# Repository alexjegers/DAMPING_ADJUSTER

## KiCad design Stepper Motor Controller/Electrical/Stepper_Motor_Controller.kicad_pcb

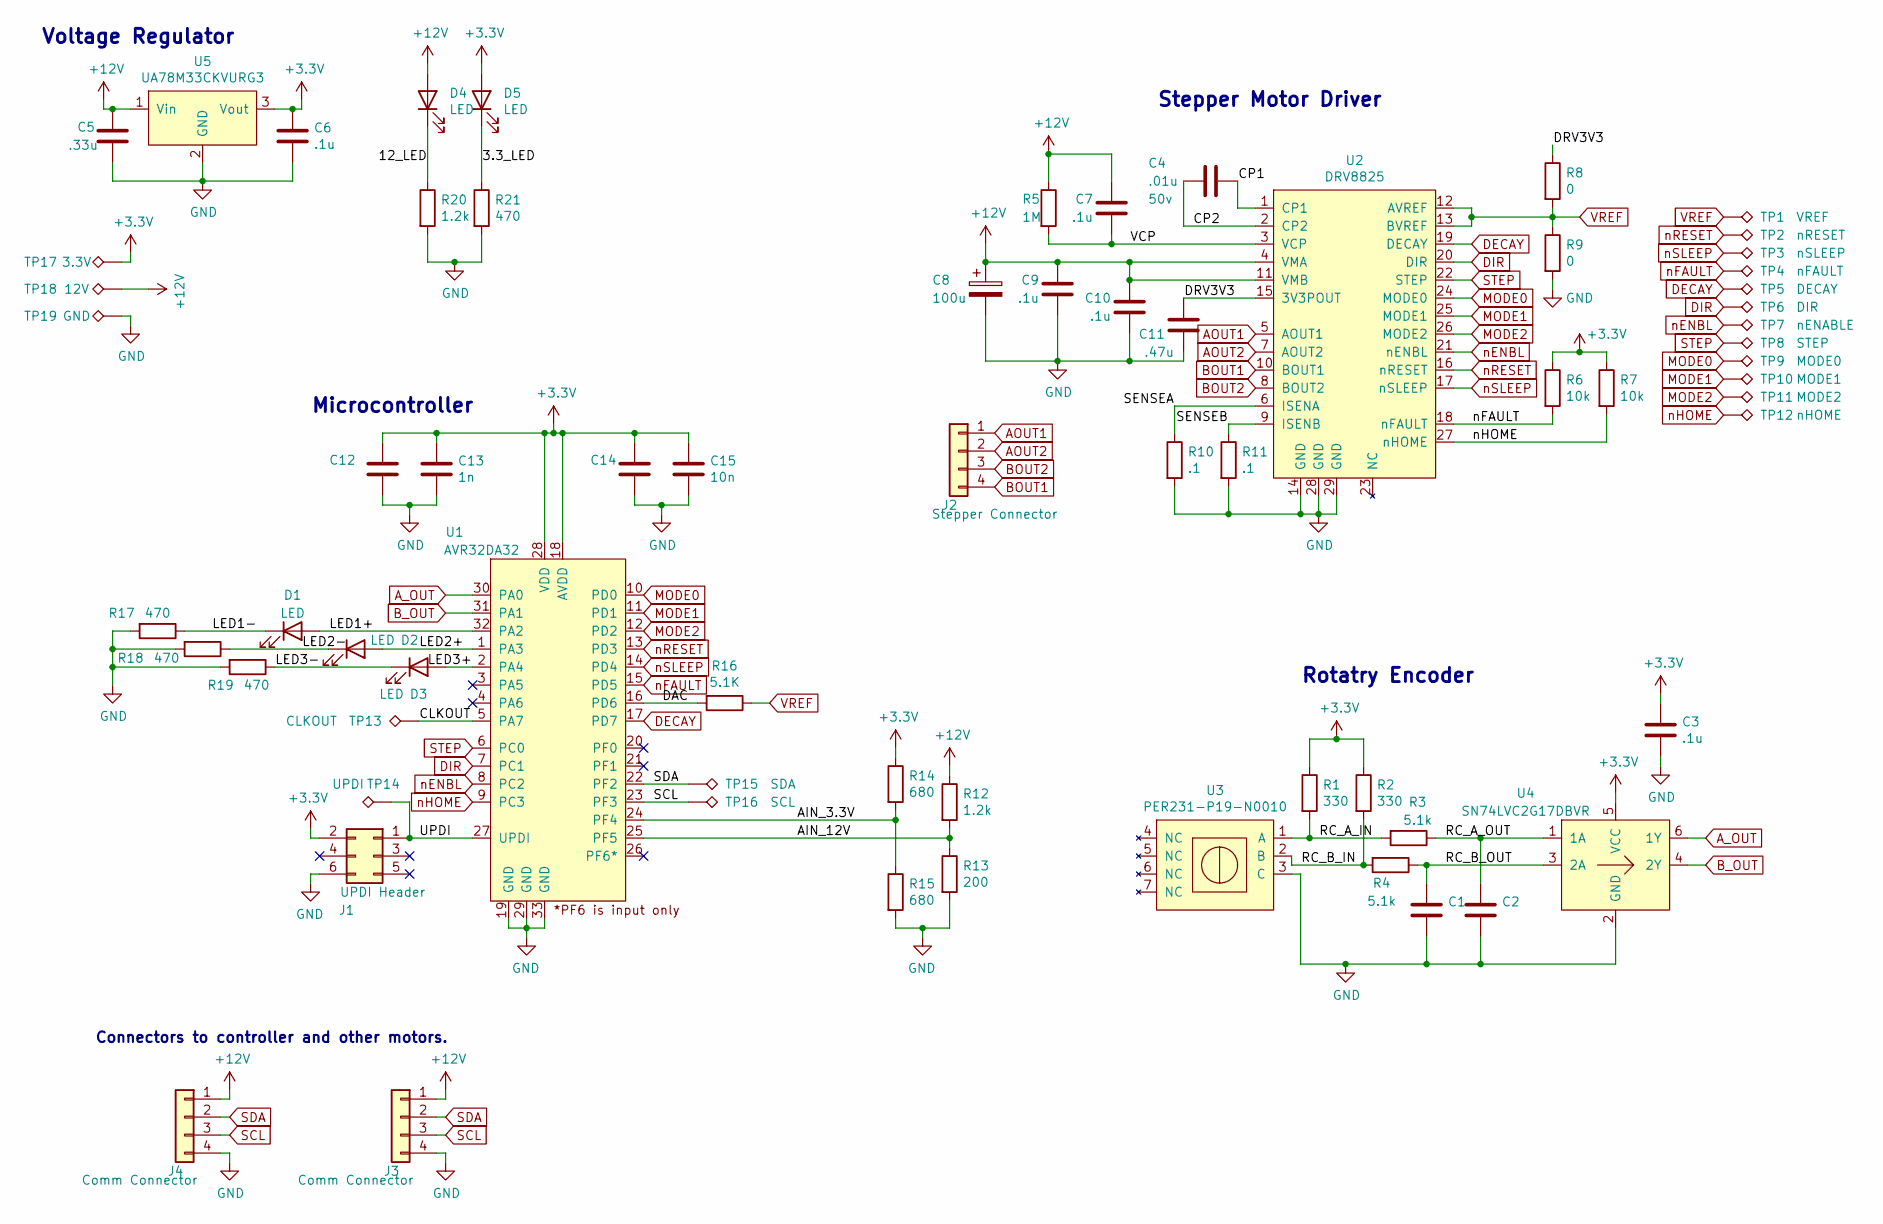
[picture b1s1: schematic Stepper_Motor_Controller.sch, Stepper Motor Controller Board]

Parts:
C1, C2, C12, C14: C_0805_2012Metric
C3, C6, C9, C10: .1u; C_0805_2012Metric
C4: .01u; C_0805_2012Metric; Voltage 50v
C5: .33u; C_0805_2012Metric
C7: .1u; C_0805_2012Metric; Voltage 16v
C8: 100u; CP_Axial_L10.0mm_D6.0mm_P15.00mm_Horizontal; MFG Part # MAL202136101E3
C11: .47u; C_0805_2012Metric; Voltage 6.3V
C13: 1n; C_0805_2012Metric
C15: 10n; C_0805_2012Metric
D1, D2, D3, D4, D5: LED; LED_1206_3216Metric
J1: UPDI Header; PinHeader_2x03_P2.54mm_Vertical
J2: Stepper Connector; 1005-003
J3, J4: Comm Connector; 1005-003
R1, R2: 330; R_0805_2012Metric
R3, R4: 5.1k; R_0805_2012Metric
R5: 1M; R_0805_2012Metric
R6, R7: 10k; R_0805_2012Metric
R8, R9: 0; R_0805_2012Metric
R10, R11: .1; R_1206_3216Metric; MFG Part # KDV12DR100ET
R12, R20: 1.2k; R_0805_2012Metric
R13: 200; R_0805_2012Metric
R14, R15: 680; R_0805_2012Metric
R16: 5.1K; R_0805_2012Metric
R17, R18, R19, R21: 470; R_0805_2012Metric
TP1: VREF; TestPoint_Pad_1.5x1.5mm
TP2: nRESET; TestPoint_Pad_1.5x1.5mm
TP3: nSLEEP; TestPoint_Pad_1.5x1.5mm
TP4: nFAULT; TestPoint_Pad_1.5x1.5mm
TP5: DECAY; TestPoint_Pad_1.5x1.5mm
TP6: DIR; TestPoint_Pad_1.5x1.5mm
TP7: nENABLE; TestPoint_Pad_1.5x1.5mm
TP8: STEP; TestPoint_Pad_1.5x1.5mm
TP9: MODE0; TestPoint_Pad_1.5x1.5mm
TP10: MODE1; TestPoint_Pad_1.5x1.5mm
TP11: MODE2; TestPoint_Pad_1.5x1.5mm
TP12: nHOME; TestPoint_Pad_1.5x1.5mm
TP13: CLKOUT; TestPoint_Pad_1.5x1.5mm
TP14: UPDI; TestPoint_Pad_1.5x1.5mm
TP15: SDA; TestPoint_Pad_1.5x1.5mm
TP16: SCL; TestPoint_Pad_1.5x1.5mm
TP17: 3.3V; TestPoint_Pad_1.5x1.5mm
TP18: 12V; TestPoint_Pad_1.5x1.5mm
TP19: GND; TestPoint_Pad_1.5x1.5mm
U1: AVR32DA32; QFN-32-1EP_5x5mm_P0.5mm_EP3.1x3.1mm
U2: DRV8825; HTSSOP-28-1EP_4.4x9.7mm_P0.65mm_EP2.85x5.4mm_ThermalVias
U3: PER231-P19-N0010
U4: SN74LVC2G17DBVR; SOT-23-6_Handsoldering
U5: UA78M33CKVURG3; TO-252-2

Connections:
+3V3: C3.1, C6.1, C12.1, C13.1, C14.1, C15.1, D5.2 (A), J1.2, R1.1, R2.1, R6.1, R7.1, R14.1, TP17.1, U1.18 (AVDD), U1.28 (VDD), U4.5 (VCC), U5.3 (Vout)
+12V: C5.1, C7.2, C8.1, C9.2, C10.2, D4.2 (A), J3.1, J4.1, R5.1, R12.1, TP18.1, U2.4 (VMA), U2.11 (VMB), U5.1 (Vin)
/3.3_LED: D5.1 (K), R21.1
/12_LED: D4.1 (K), R20.1
/AIN_3.3V: R14.2, R15.1, U1.24 (PF4)
/AIN_12V: R12.2, R13.1, U1.25 (PF5)
/CLKOUT: TP13.1, U1.5 (PA7)
/CP1: C4.2, U2.1 (CP1)
/CP2: C4.1, U2.2 (CP2)
/DAC: R16.2, U1.16 (PD6)
/DRV3V3: C11.2, R8.1, U2.15 (3V3POUT)
/LED1+: D1.2 (A), U1.32 (PA2)
/LED1-: D1.1 (K), R17.1
/LED2+: D2.2 (A), U1.1 (PA3)
/LED2-: D2.1 (K), R18.1
/LED3+: D3.2 (A), U1.2 (PA4)
/LED3-: D3.1 (K), R19.1
/RC_A_IN: R1.2, R3.2, U3.1 (A)
/RC_A_OUT: C2.1, R3.1, U4.1 (1A)
/RC_B_IN: R2.2, R4.2, U3.2 (B)
/RC_B_OUT: C1.1, R4.1, U4.3 (2A)
/SENSEA: R10.1, U2.6 (ISENA)
/SENSEB: R11.1, U2.9 (ISENB)
/UPDI: J1.1, TP14.1, U1.27 (UPDI)
/VCP: C7.1, R5.2, U2.3 (VCP)
AOUT1: J2.1, U2.5 (AOUT1)
AOUT2: J2.2, U2.7 (AOUT2)
A_OUT: U1.30 (PA0), U4.6 (1Y)
BOUT1: J2.4, U2.10 (BOUT1)
BOUT2: J2.3, U2.8 (BOUT2)
B_OUT: U1.31 (PA1), U4.4 (2Y)
DECAY: TP5.1, U1.17 (PD7), U2.19 (DECAY)
DIR: TP6.1, U1.7 (PC1), U2.20 (DIR)
GND: C1.2, C2.2, C3.2, C5.2, C6.2, C8.2, C9.1, C10.1, C11.1, C12.2, C13.2, C14.2, C15.2, J1.6, J3.4, J4.4, R9.2, R10.2, R11.2, R13.2, R15.2, R17.2, R18.2, R19.2, R20.2, R21.2, TP19.1, U1.19 (GND), U1.29 (GND), U1.33 (GND), U2.14 (GND), U2.28 (GND), U2.29 (GND), U3.3 (C), U4.2 (GND), U5.2 (GND)
MODE0: TP9.1, U1.10 (PD0), U2.24 (MODE0)
MODE1: TP10.1, U1.11 (PD1), U2.25 (MODE1)
MODE2: TP11.1, U1.12 (PD2), U2.26 (MODE2)
SCL: J3.3, J4.3, TP16.1, U1.23 (PF3)
SDA: J3.2, J4.2, TP15.1, U1.22 (PF2)
STEP: TP8.1, U1.6 (PC0), U2.22 (STEP)
VREF: R8.2, R9.1, R16.1, TP1.1, U2.12 (AVREF), U2.13 (BVREF)
nENBL: TP7.1, U1.8 (PC2), U2.21 (nENBL)
nFAULT: R6.2, TP4.1, U1.15 (PD5), U2.18 (nFAULT)
nHOME: R7.2, TP12.1, U1.9 (PC3), U2.27 (nHOME)
nRESET: TP2.1, U1.13 (PD3), U2.16 (nRESET)
nSLEEP: TP3.1, U1.14 (PD4), U2.17 (nSLEEP)

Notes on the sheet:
Connectors to controller and other motors.
Microcontroller
Voltage Regulator
Stepper Motor Driver
Rotatry Encoder

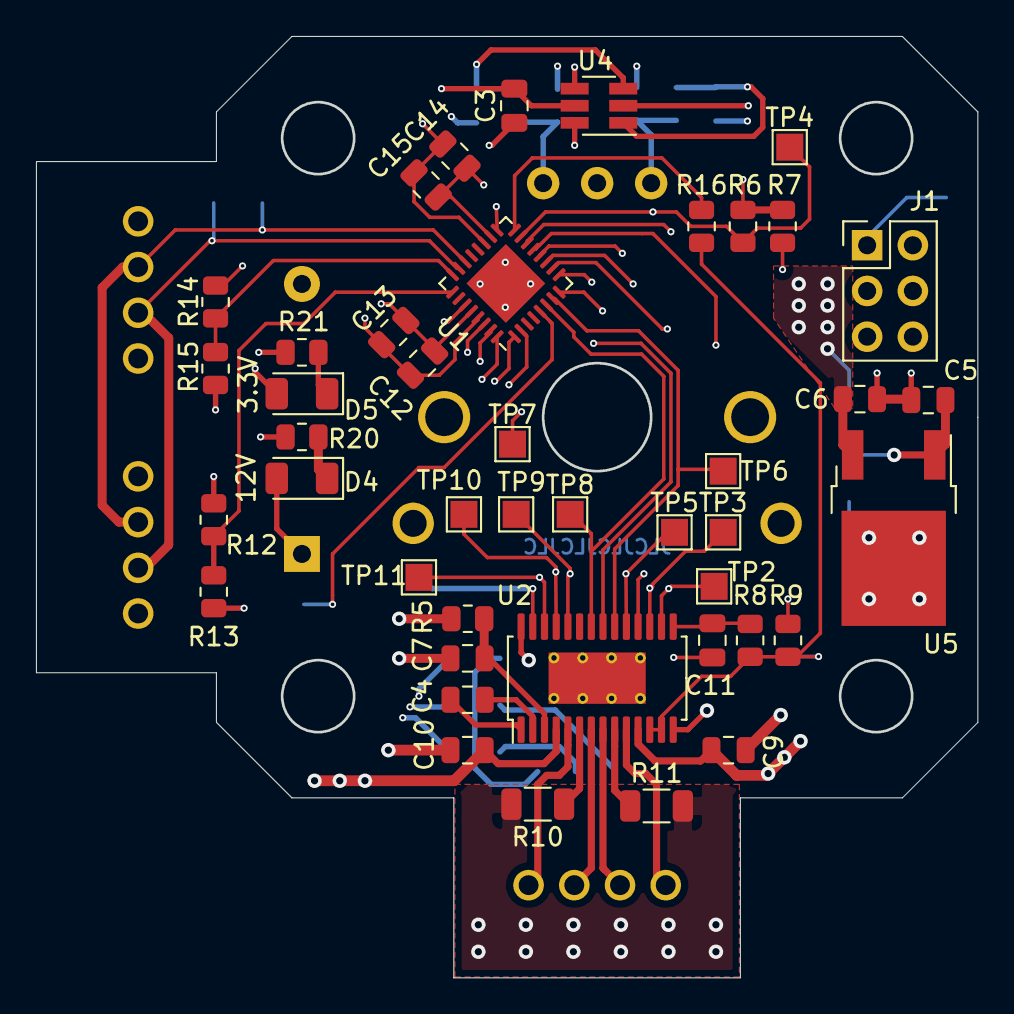
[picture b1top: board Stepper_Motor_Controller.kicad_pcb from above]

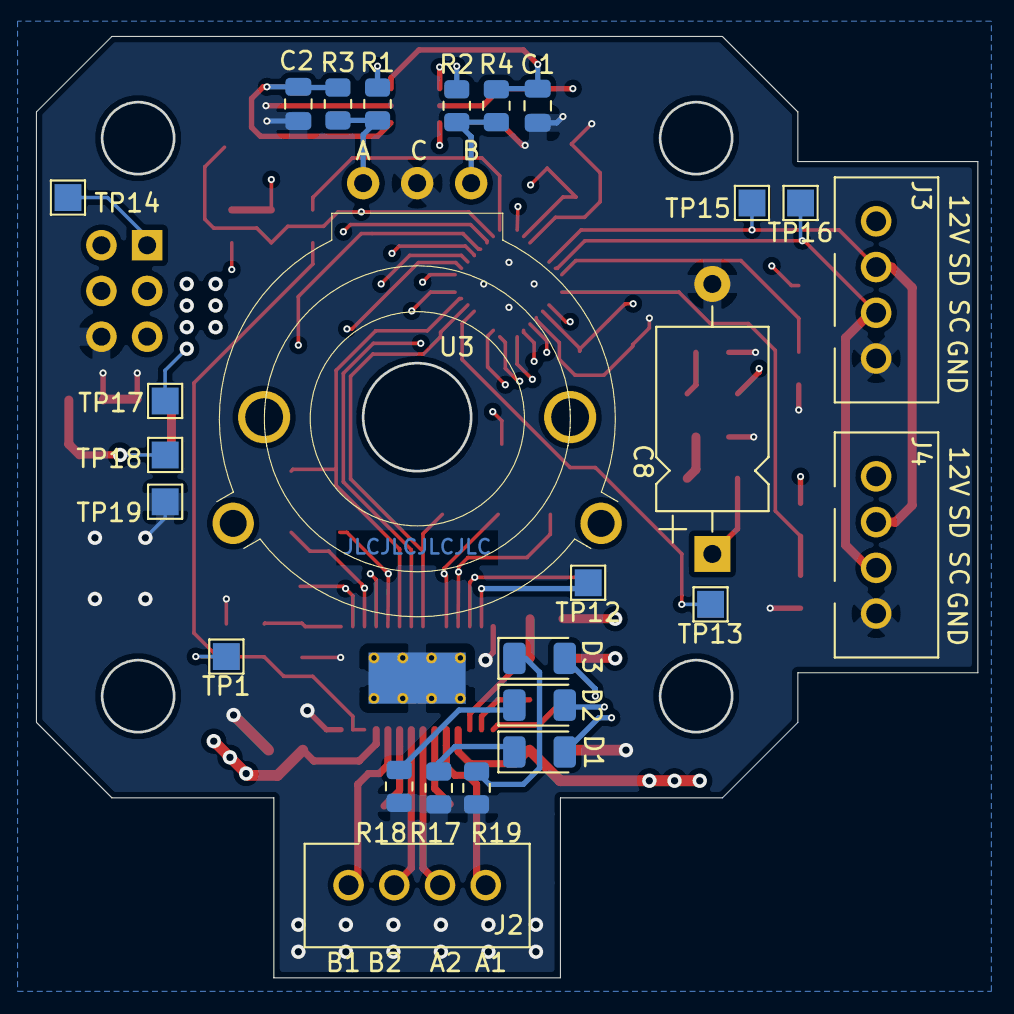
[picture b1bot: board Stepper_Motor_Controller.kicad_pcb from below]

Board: 4 copper layers, 52.2 x 52.2 mm, 69 parts (26 on the bottom side), 46 nets.

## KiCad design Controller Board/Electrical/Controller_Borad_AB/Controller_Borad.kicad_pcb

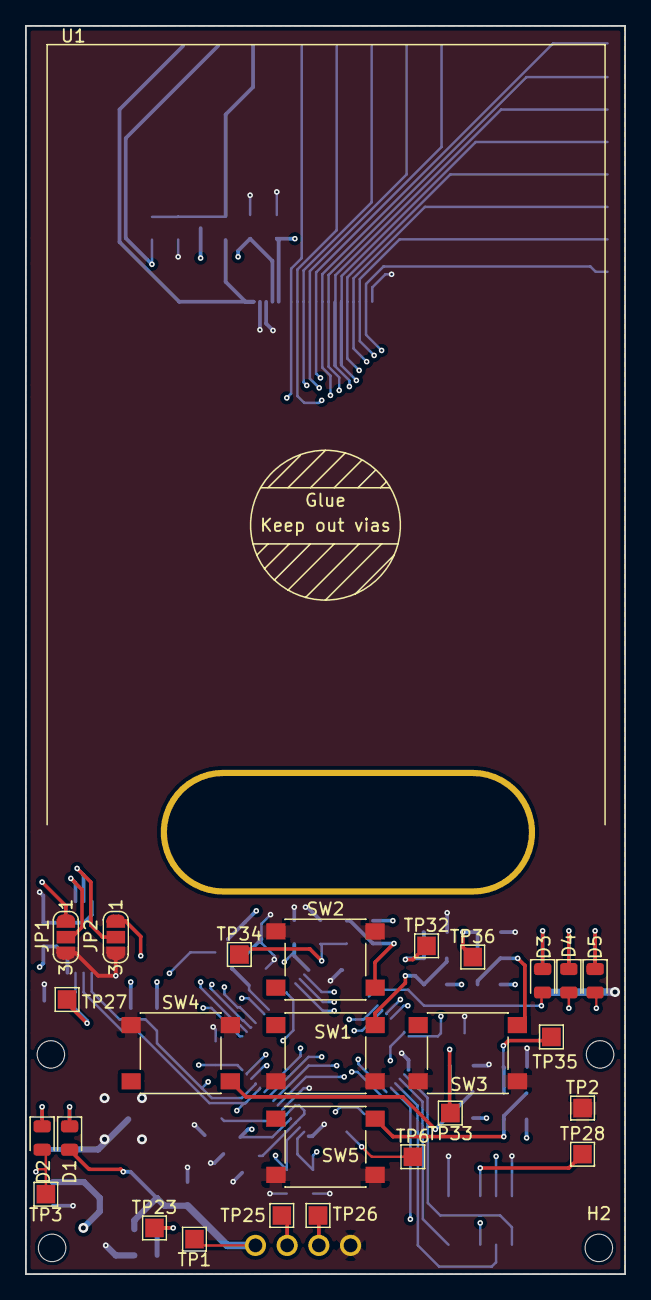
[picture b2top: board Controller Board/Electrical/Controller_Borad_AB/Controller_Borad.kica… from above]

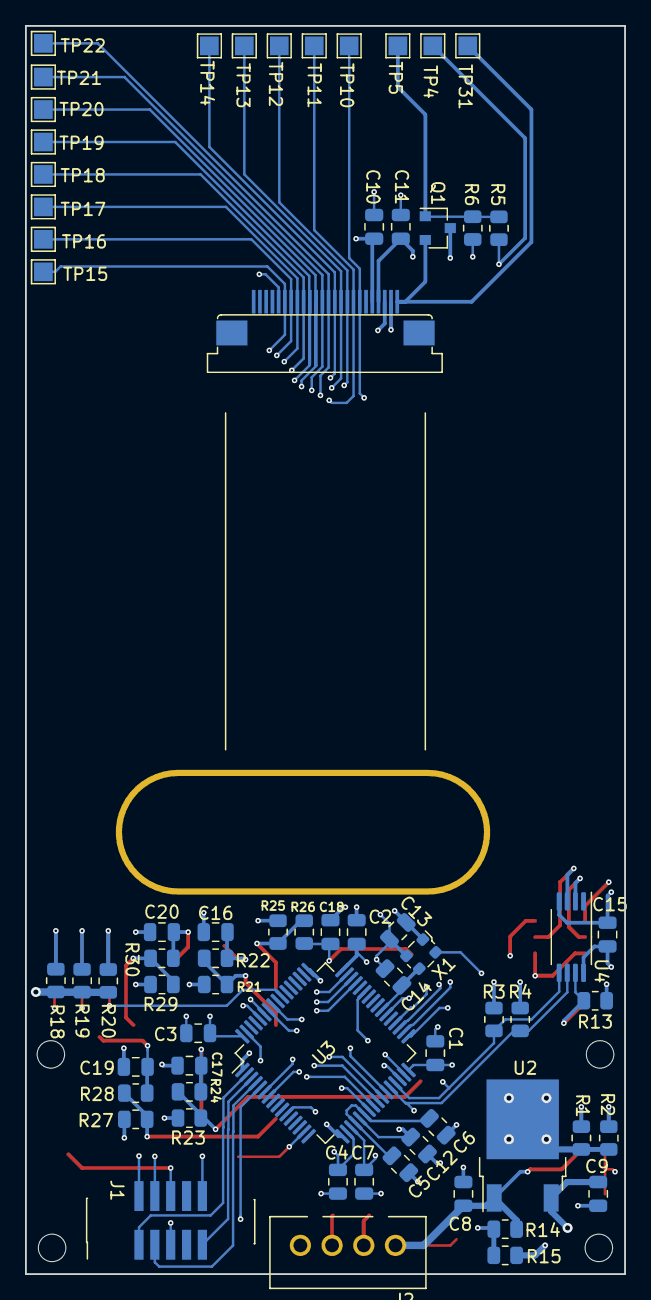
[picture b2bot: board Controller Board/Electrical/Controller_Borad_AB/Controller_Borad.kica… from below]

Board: 4 copper layers, 48.0 x 100.0 mm, 96 parts (65 on the bottom side), 51 nets.

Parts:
C1, C3, C4, C5, C7, C9, C10, C12, C13, C15: .1u; C_0805_2012Metric
C2, C6, C16, C17, C18, C19, C20: 1u; C_0805_2012Metric
C8: .33u; C_0805_2012Metric
C11: 10u; C_0805_2012Metric
C14: 10p; C_0805_2012Metric
D1, D2: LED; LED_0805_2012Metric
D3: LED1; LED_0805_2012Metric
D4: LED2; LED_0805_2012Metric
D5: LED3; LED_0805_2012Metric
H1, H2, H3, H4: MountingHole; MountingHole_2.2mm_M2
J1: JTAG Connector; PinHeader_2x05_P1.27mm_Vertical_SMD
J2: Comm Connector; 1005-003
JP1, JP2: A1; SolderJumper-3_P1.3mm_Open_RoundedPad1.0x1.5mm_NumberLabels
Q1: BSR802N; SOT-23
R1: 3.3k; R_0805_2012Metric
R2, R14: 1.2k; R_0805_2012Metric
R3, R4: 1k; R_0805_2012Metric
R5, R15: 200; R_0805_2012Metric
R6: 47k; R_0805_2012Metric
R13, R22, R24, R26, R28, R30: 10k; R_0805_2012Metric
R18, R19, R20: 470; R_0805_2012Metric
R21, R23, R25, R27, R29: 330; R_0805_2012Metric
SW1, SW2, SW3, SW4, SW5: SW_Push; SW_Push_1P1T_NO_6x6mm_H9.5mm
TP1: 12V; TestPoint_Pad_1.5x1.5mm
TP2: GND; TestPoint_Pad_1.5x1.5mm
TP3: 3.3V; TestPoint_Pad_1.5x1.5mm
TP4: LCD PWM; TestPoint_Pad_1.5x1.5mm
TP5: LCD PWM GDR; TestPoint_Pad_1.5x1.5mm
TP6: GCLK2; TestPoint_Pad_1.5x1.5mm
TP10: LCD_CS; TestPoint_Pad_1.5x1.5mm
TP11: LCD_RESET; TestPoint_Pad_1.5x1.5mm
TP12: LCD_RS; TestPoint_Pad_1.5x1.5mm
TP13: LCD_WR; TestPoint_Pad_1.5x1.5mm
TP14: LCD_RD; TestPoint_Pad_1.5x1.5mm
TP15: D0; TestPoint_Pad_1.5x1.5mm
TP16: D1; TestPoint_Pad_1.5x1.5mm
TP17: D2; TestPoint_Pad_1.5x1.5mm
TP18: D3; TestPoint_Pad_1.5x1.5mm
TP19: D4; TestPoint_Pad_1.5x1.5mm
TP20: D5; TestPoint_Pad_1.5x1.5mm
TP21: D6; TestPoint_Pad_1.5x1.5mm
TP22: D7; TestPoint_Pad_1.5x1.5mm
TP23: AIN_12V; TestPoint_Pad_1.5x1.5mm
TP25: SDA; TestPoint_Pad_1.5x1.5mm
TP26: SCL; TestPoint_Pad_1.5x1.5mm
TP27: EEPROM_WR; TestPoint_Pad_1.5x1.5mm
TP28: RESET_N; TestPoint_Pad_1.5x1.5mm
TP31: LCD_LED+; TestPoint_Pad_1.5x1.5mm
TP32: BT_1; TestPoint_Pad_1.5x1.5mm
TP33: BT_4; TestPoint_Pad_1.5x1.5mm
TP34: BT_2; TestPoint_Pad_1.5x1.5mm
TP35: BT_5; TestPoint_Pad_1.5x1.5mm
TP36: BT_3; TestPoint_Pad_1.5x1.5mm
U1: RY24049B0-00
U2: UA78M33CKVURG3; TO-252-2
U3: ATUC128D3; TQFP-64_10x10mm_P0.5mm
U4: AT24C04D; TSSOP-8_4.4x3mm_P0.65mm
X1: ECS-2520MV-480; Oscillator_SMD_ECS_2520MV-xxx-xx-4Pin_2.5x2.0mm

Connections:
+1V8: C5.1, C6.1, U3.20, U3.22
+3V3: C1.1, C2.1, C3.1, C4.1, C7.1, C9.1, C10.1, C11.1, C12.1, C13.1, C15.1, D2.2, J1.4, JP1.1, JP2.1, Q1.3, R3.1, R4.1, R21.1, R23.1, R25.1, R27.1, R29.1, TP3.1, U1.4, U1.5, U2.3, U3.18, U3.19, U3.21, U3.32, U3.48, U3.64, U4.8, X1.1, X1.4
+12V: C8.1, D1.2, J2.1, R14.1, TP1.1, U2.1
/ADDR_1: JP1.2, U4.2
/ADDR_2: JP2.2, U4.3
/AIN_12V: R14.2, R15.1, TP23.1, U3.11
/BT_1: C16.1, R22.1, TP32.1, U3.45
/BT_2: C18.1, R26.1, TP34.1, U3.46
/BT_3: C20.1, R30.1, TP36.1, U3.47
/BT_4: C17.1, R24.1, TP33.1, U3.59
/BT_5: C19.1, R28.1, TP35.1, U3.60
/Controller Board Buttons/SW1+: R21.2, R22.2, SW1.2
/Controller Board Buttons/SW2+: R25.2, R26.2, SW2.2
/Controller Board Buttons/SW3+: R29.2, R30.2, SW3.2
/Controller Board Buttons/SW4+: R23.2, R24.2, SW4.2
/Controller Board Buttons/SW5+: R27.2, R28.2, SW5.2
/EEPROM_WP: R13.1, TP27.1, U4.7
/GLCK2: TP6.1, U3.15
/LCD_GDR: Q1.1, R5.1, R6.1, TP5.1
/LCD_LED+: Q1.2, TP31.1, U1.1
/LED1-: D3.1, R20.1
/LED2-: D4.1, R19.1
/LED3-: D5.1, R18.1
/LED_3.3V: D2.1, R2.1
/LED_12V: D1.1, R1.1
/SCL: J2.3, R4.2, TP26.1, U3.28, U4.6
/SDA: J2.2, R3.2, TP25.1, U3.29, U4.5
D0: TP15.1, U1.19, U3.6
D1: TP16.1, U1.18, U3.7
D2: TP17.1, U1.17, U3.24
D3: TP18.1, U1.16, U3.25
D4: TP19.1, U1.15, U3.26
D5: TP20.1, U1.14, U3.27
D6: TP21.1, U1.13, U3.38
D7: TP22.1, U1.12, U3.43
GND: C1.2, C2.2, C3.2, C4.2, C5.2, C6.2, C7.2, C8.2, C9.2, C10.2, C11.2, C12.2, C13.2, C14.2, C15.2, C16.2, C17.2, C18.2, C19.2, C20.2, J1.2, J1.10, J2.4, JP1.3, JP2.3, R1.2, R2.2, R6.2, R13.2, R15.2, R18.2, R19.2, R20.2, SW1.1, SW2.1, SW3.1, SW4.1, SW5.1, TP2.1, U1.2, U1.3, U1.20, U2.2, U3.1, U3.17, U3.23, U3.49, U4.4, X1.2
LCD_CS: TP10.1, U1.7, U3.31
LCD_PWM: R5.2, TP4.1, U3.30
LCD_RD: TP14.1, U1.11, U3.33
LCD_RESET: TP11.1, U1.8, U3.36
LCD_RS: TP12.1, U1.9, U3.34
LCD_WR: TP13.1, U1.10, U3.35
LED+_1: D3.2, U3.55
LED+_2: D4.2, U3.57
LED+_3: D5.2, U3.58
RESET_N: J1.6, TP28.1, U3.63
TCK: J1.1, U3.2
TDI: J1.9, U3.3
TDO: J1.3, U3.4
TMS: J1.5, U3.5
XIN: C14.1, U3.39, X1.3

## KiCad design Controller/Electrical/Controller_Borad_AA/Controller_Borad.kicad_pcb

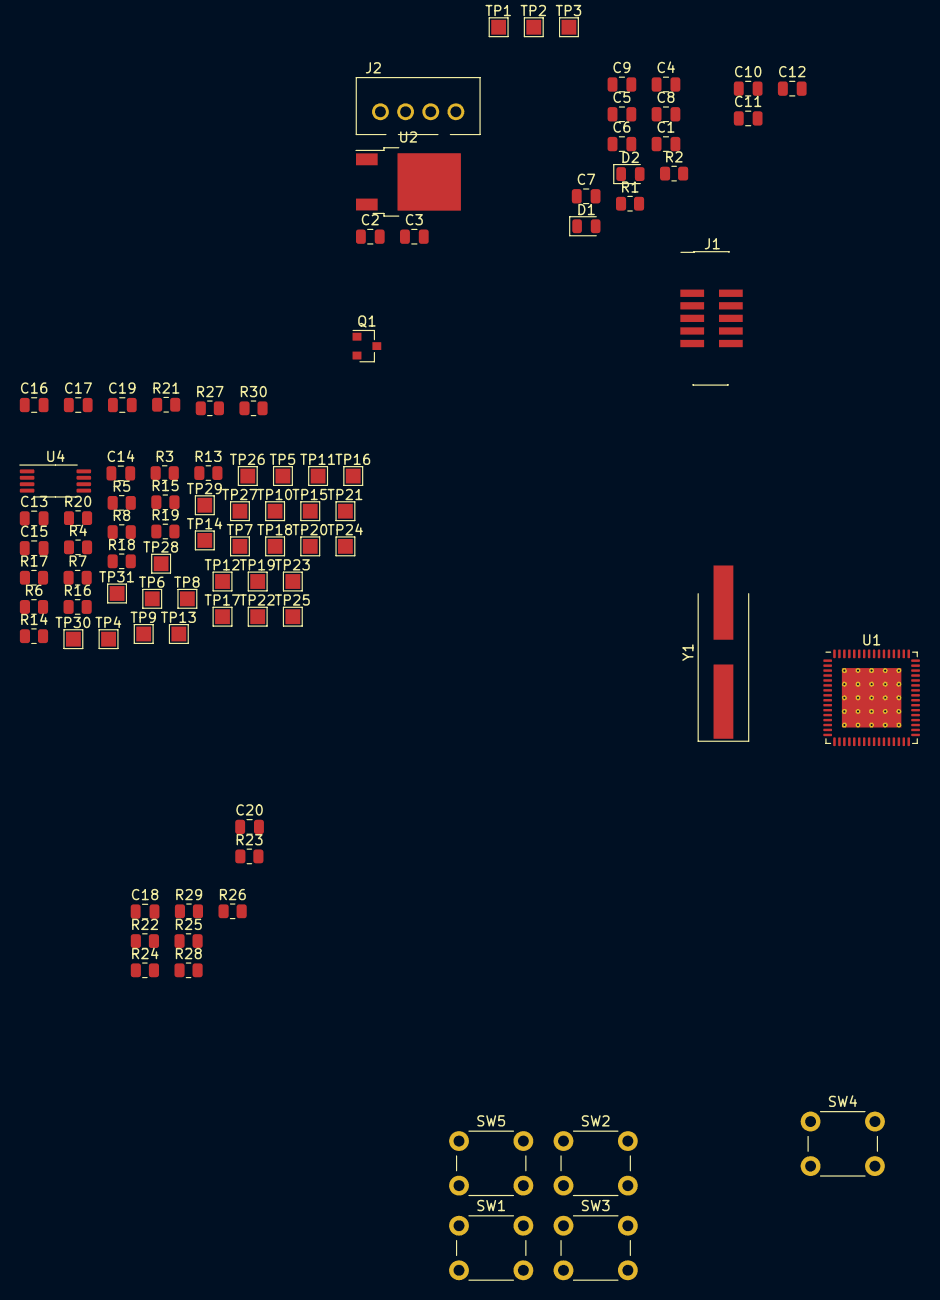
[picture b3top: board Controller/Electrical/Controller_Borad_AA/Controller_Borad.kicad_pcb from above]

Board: 2 copper layers, 91 parts (0 on the bottom side), 50 nets, no tracks yet.

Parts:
C1, C3, C4, C5, C7, C9, C10, C12, C15: .1u; C_0805_2012Metric
C2, C6, C16, C17, C18, C19, C20: 1u; C_0805_2012Metric
C8: .33u; C_0805_2012Metric
C11: 10u; C_0805_2012Metric
C13, C14: 14p; C_0805_2012Metric
D1, D2: LED; LED_0805_2012Metric
J1: JTAG Connector; PinHeader_2x05_P1.27mm_Vertical_SMD
J2: Comm Connector; 1005-003
Q1: BSR802N; SOT-23
R1: 1.5k; R_0805_2012Metric
R2, R18, R19, R20: 470; R_0805_2012Metric
R3, R4: 1k; R_0805_2012Metric
R5, R15: 200; R_0805_2012Metric
R6: 47k; R_0805_2012Metric
R7, R8, R14: 1.2k; R_0805_2012Metric
R13, R22, R24, R26, R28, R30: 10k; R_0805_2012Metric
R16, R17: 680; R_0805_2012Metric
R21, R23, R25, R27, R29: 330; R_0805_2012Metric
SW1, SW2, SW3, SW4, SW5: SW_Push; SW_PUSH_6mm_H5mm
TP1: 12V; TestPoint_Pad_1.5x1.5mm
TP2: GND; TestPoint_Pad_1.5x1.5mm
TP3: 3.3V; TestPoint_Pad_1.5x1.5mm
TP4: LCD PWM; TestPoint_Pad_1.5x1.5mm
TP5: LCD PWM GDR; TestPoint_Pad_1.5x1.5mm
TP6: GCLK0; TestPoint_Pad_1.5x1.5mm
TP7: GCLK1; TestPoint_Pad_1.5x1.5mm
TP8: GCLK2; TestPoint_Pad_1.5x1.5mm
TP9: GCLK3; TestPoint_Pad_1.5x1.5mm
TP10: LCD_CS; TestPoint_Pad_1.5x1.5mm
TP11: LCD_RESET; TestPoint_Pad_1.5x1.5mm
TP12: LCD_RS; TestPoint_Pad_1.5x1.5mm
TP13: LCD_WR; TestPoint_Pad_1.5x1.5mm
TP14: LCD_RD; TestPoint_Pad_1.5x1.5mm
TP15: D0; TestPoint_Pad_1.5x1.5mm
TP16: D1; TestPoint_Pad_1.5x1.5mm
TP17: D2; TestPoint_Pad_1.5x1.5mm
TP18: D3; TestPoint_Pad_1.5x1.5mm
TP19: D4; TestPoint_Pad_1.5x1.5mm
TP20: D5; TestPoint_Pad_1.5x1.5mm
TP21: D6; TestPoint_Pad_1.5x1.5mm
TP22: D7; TestPoint_Pad_1.5x1.5mm
TP23: AIN_12V; TestPoint_Pad_1.5x1.5mm
TP24: AIN_3.3V; TestPoint_Pad_1.5x1.5mm
TP25: SDA_3; TestPoint_Pad_1.5x1.5mm
TP26: SCL_3; TestPoint_Pad_1.5x1.5mm
TP27: EEPROM_WR; TestPoint_Pad_1.5x1.5mm
TP28: RESET_N; TestPoint_Pad_1.5x1.5mm
TP29: SDA_2; TestPoint_Pad_1.5x1.5mm
TP30: SCL_2; TestPoint_Pad_1.5x1.5mm
TP31: LCD_LED+; TestPoint_Pad_1.5x1.5mm
U1: ATSAM4LC2BA; QFN-64-1EP_9x9mm_P0.5mm_EP6x6mm_ThermalVias
U2: UA78M33CKVURG3; TO-252-2
U4: AT24C04D; TSSOP-8_4.4x3mm_P0.65mm
Y1: 30MHz; Crystal_SMD_HC49-SD_HandSoldering

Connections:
+1V8: C5.1, C6.1, U1.5, U1.7
+3V3: C1.1, C2.1, C3.1, C4.1, C7.1, C9.1, C10.1, C11.1, C12.1, C15.1, D2.2, J1.1, Q1.3, R3.1, R4.1, R7.1, R8.1, R16.1, R21.1, R23.1, R25.1, R27.1, R29.1, TP3.1, U1.8, U1.24, U1.25, U1.39, U1.52, U1.61, U2.3, U4.8
+12V: C8.1, D1.2, J2.1, R14.1, TP1.1, U2.1
/AIN_3.3V: R16.2, R17.1, TP24.1, U1.15
/AIN_12V: R14.2, R15.1, TP23.1, U1.16
/BT_1: C16.1, R22.1, U1.41
/BT_2: C18.1, R26.1, U1.42
/BT_3: C20.1, R30.1, U1.43
/BT_4: C17.1, R24.1, U1.44
/BT_5: C19.1, R28.1, U1.49
/Controller Board Buttons/SW1+: R21.2, R22.2, SW1.2
/Controller Board Buttons/SW2+: R25.2, R26.2, SW3.2
/Controller Board Buttons/SW3+: R29.2, R30.2, SW5.2
/Controller Board Buttons/SW4+: R23.2, R24.2, SW2.2
/Controller Board Buttons/SW5+: R27.2, R28.2, SW4.2
/EEPROM_WP: R13.1, TP27.1, U1.46, U4.7
/GCLK1: TP7.1, U1.48
/GCLK2: TP8.1, U1.53
/GCLK3: TP9.1, U1.54
/GLCK0: TP6.1, U1.47
/LCD_GDR: Q1.1, R5.1, R6.1, TP5.1
/LCD_LED+: Q1.2, TP31.1
/LED_3.3V: D2.1, R2.1
/LED_12V: D1.1, R1.1
/SCL_2: J2.3, R3.2, TP30.1, U1.56
/SCL_3: R8.2, TP26.1, U1.58, U4.6
/SDA_2: J2.2, R4.2, TP29.1, U1.55
/SDA_3: R7.2, TP25.1, U1.57, U4.5
/XIN: C13.1, U1.1, Y1.1
/XOUT: C14.1, U1.2, Y1.2
D0: TP15.1, U1.11
D1: TP16.1, U1.12
D2: TP17.1, U1.13
D3: TP18.1, U1.14
D4: TP19.1, U1.19
D5: TP20.1, U1.20
D6: TP21.1, U1.27
D7: TP22.1, U1.28
GND: C1.2, C2.2, C3.2, C4.2, C5.2, C6.2, C7.2, C8.2, C9.2, C10.2, C11.2, C12.2, C13.2, C14.2, C15.2, C16.2, C17.2, C18.2, C19.2, C20.2, J1.3, J1.5, J1.9, J2.4, R1.2, R2.2, R6.2, R13.2, R15.2, R17.2, R18.2, R19.2, R20.2, SW1.1, SW2.1, SW3.1, SW4.1, SW5.1, TP2.1, U1.6, U1.23, U1.38, U1.64, U1.65, U2.2, U4.4
LCD_CS: TP10.1, U1.29
LCD_PWM: R5.2, TP4.1, U1.26
LCD_RD: TP14.1, U1.30
LCD_RESET: TP11.1, U1.40
LCD_RS: TP12.1, U1.31
LCD_WR: TP13.1, U1.32
RESET_N: J1.10, TP28.1, U1.4
TCK: J1.4, U1.9
TDI: J1.8, U1.60
TDO: J1.6, U1.59
TMS: J1.2, U1.10

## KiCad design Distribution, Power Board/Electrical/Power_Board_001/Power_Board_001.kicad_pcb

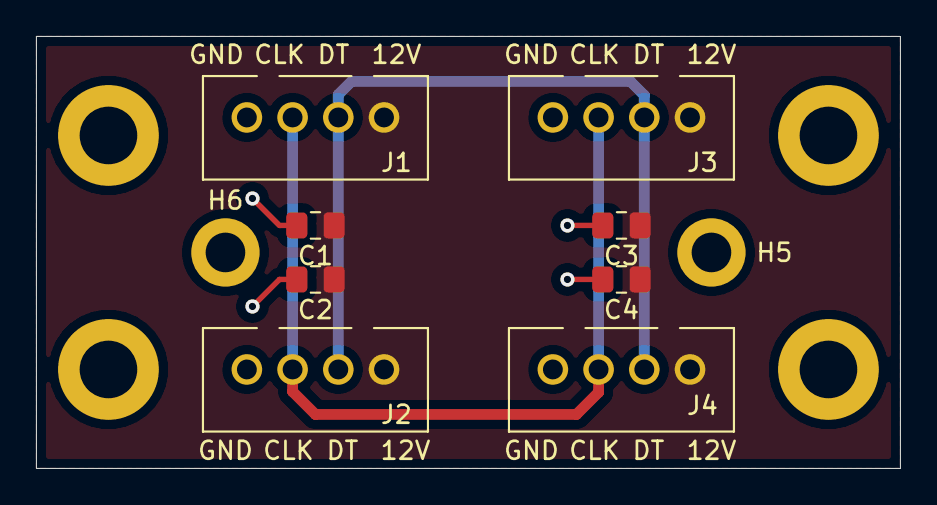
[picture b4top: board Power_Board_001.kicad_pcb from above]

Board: 2 copper layers, 48.0 x 24.0 mm, 14 parts (0 on the bottom side), 4 nets.

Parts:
C1, C2, C3, C4: .1u; C_0805_2012Metric_Pad1.18x1.45mm_HandSolder
H1, H2, H3, H4: MountingHole_Pad; MountingHole_3.2mm_M3_DIN965_Pad
H5, H6: MountingHole_Pad; MountingHole_2.2mm_M2_DIN965_Pad
J1, J2, J3, J4: Comm_Connector; 1005-003

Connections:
+12V: C1.1, C2.1, C3.1, C4.1, J1.1, J2.1, J3.1, J4.1
GND: C1.2, C2.2, C3.2, C4.2, H1.1, H2.1, H3.1, H4.1, H5.1, H6.1, J1.4, J2.4, J3.4, J4.4
SCL: J1.3, J2.3, J3.3, J4.3
SDA: J1.2, J2.2, J3.2, J4.2

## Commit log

2022-10-05 File Organization
2022-10-05 File Orginization
2022-10-06 Added power and distribution board enclosure part
2022-10-06 Small changes
2022-10-06 Rebuild
2022-10-06 New revisions
2022-10-07 Decreased thread revolutions
2022-10-07 stepperGoToZero function improvements
2022-10-11 Testing for GoToZero function
2022-10-11 Updated comments and annotations
2022-10-11 Shorted hex key
2022-10-11 New versions
2022-10-11 Updated for encoder signal processing testing
2022-10-11 Created mold for carbon fiber.
2022-10-11 Widened area for LCD
2022-10-11 Initial release
2022-10-11 Not ignoring files types that it should be
2022-10-19 Enlarged hole for connectors on back.
2022-10-19 No change
2022-10-19 In Progress
2022-10-25 Commit before I redo LCD.cpp
2022-11-04 Added button and label classes
2022-11-11 Tons of LCD display stuff, started IIC comm.
2022-11-11 State diagrams for LCD display states
2022-11-11 Stupid bug that was just a bad solder joint
    D7 bit of data bus had a bad solder joint.
2022-11-11 Final edits and printed enclosure for power board
2022-11-11 LCD testing and debugging
2022-11-11 Screenshots
2022-11-11 Added setPosition function for stepper motor
2022-11-14 New schematic and PCB version AC
2022-11-14 Added annotations
2022-11-15 Fix errors in schematic from Ver. AB
2022-11-15 Create IIC FIFO buffer
2022-11-15 Added schematic JPGs
2022-11-15 File Management
2022-11-22 Fixed TWI bugs
2022-11-22 Renamed folders
2022-12-20 Added circles and rounded rectangles
2022-12-20 Added rounded buttons. Label strings fixed length .
2022-12-20 Stops working after a slave NACK
2022-12-20 Restructured for new slave address format.
2022-12-20 Misc changes
2022-12-20 Updated to reflect new procedure
2022-12-20 Error flags updated
2022-12-20 Fixed bug when calculating max offset
2022-12-20 Added DXF and new config for CNC machining
